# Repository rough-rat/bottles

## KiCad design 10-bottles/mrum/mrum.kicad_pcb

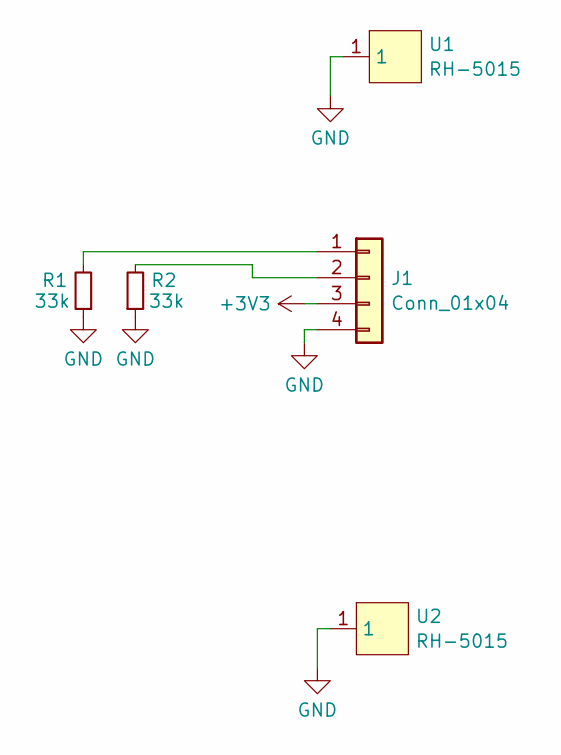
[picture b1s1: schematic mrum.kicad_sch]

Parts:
J1: Conn_01x04; PinHeader_1x04_P2.54mm_Vertical_SMD_Pin1Left
R1, R2: 33k; R_0603_1608Metric_Pad0.98x0.95mm_HandSolder
U1, U2: RH-5015; SMD_RH-5015; LCSC Part C5199798

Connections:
+3V3: J1.3
GND: J1.4, R1.1, R2.1, U1.1, U2.1
unnamed: J1.1, R1.2
unnamed: J1.2, R2.2

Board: 2 copper layers, 5 parts (5 on the bottom side), 3 nets, no tracks yet.

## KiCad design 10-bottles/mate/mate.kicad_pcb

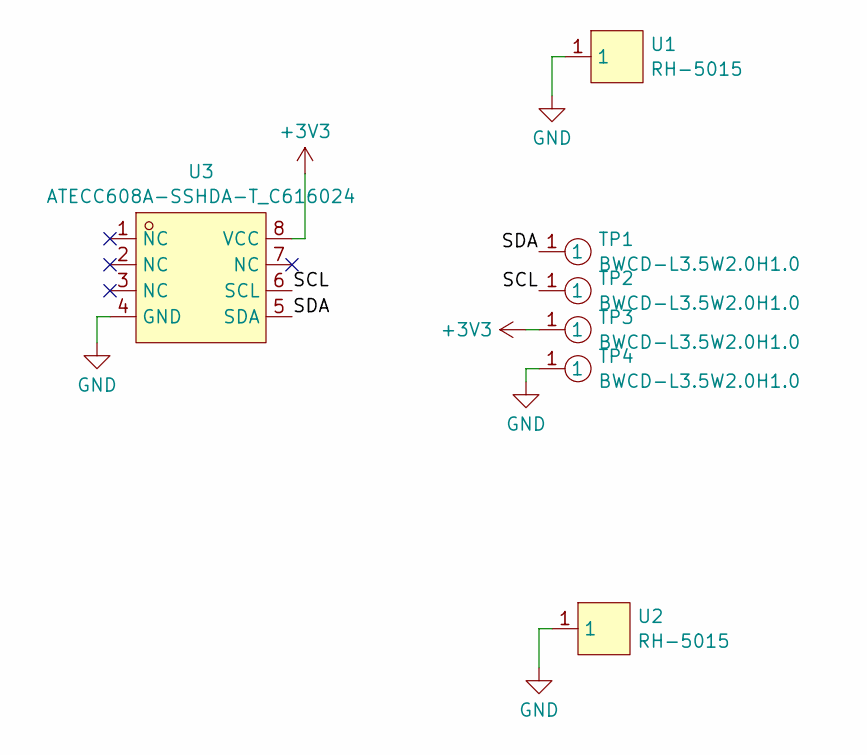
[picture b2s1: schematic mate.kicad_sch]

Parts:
TP1, TP2, TP3, TP4: BWCD-L3.5W2.0H1.0; SMD_BD2.0-L2.0-W2.0_C9900001905; LCSC Part C2826547
U1, U2: RH-5015; SMD_RH-5015; LCSC Part C5199798
U3: ATECC608A-SSHDA-T_C616024; SOIC-8_L4.9-W3.9-P1.27-LS6.0-BL; LCSC Part C616024

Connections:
+3V3: TP3.1, U3.8 (VCC)
/SCL: TP2.1, U3.6 (SCL)
/SDA: TP1.1, U3.5 (SDA)
GND: TP4.1, U1.1, U2.1, U3.4 (GND)

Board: 2 copper layers, 7 parts (7 on the bottom side), 4 nets, no tracks yet.

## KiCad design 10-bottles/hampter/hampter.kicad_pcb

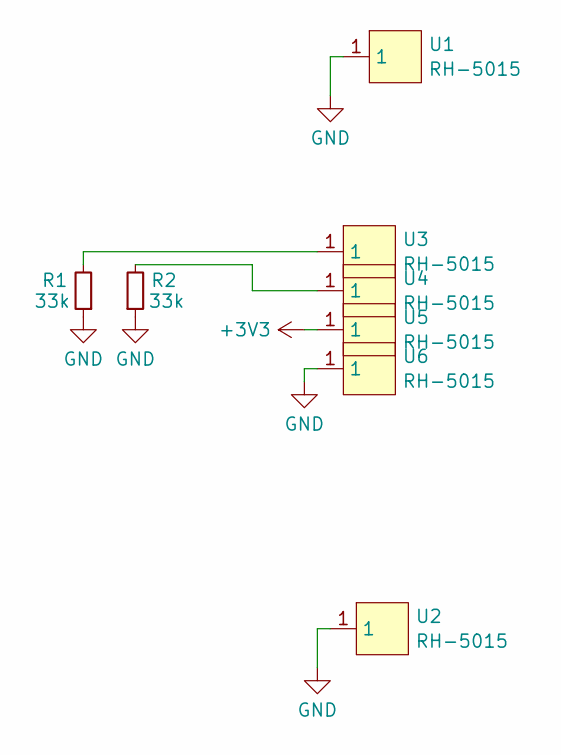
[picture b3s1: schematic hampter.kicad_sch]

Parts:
R1, R2: 33k; R_0603_1608Metric_Pad0.98x0.95mm_HandSolder
U1, U2, U3, U4, U5, U6: RH-5015; SMD_RH-5015; LCSC Part C5199798

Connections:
+3V3: U5.1
GND: R1.1, R2.1, U1.1, U2.1, U6.1
unnamed: R1.2, U3.1
unnamed: R2.2, U4.1

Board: 2 copper layers, 8 parts (8 on the bottom side), 3 nets, no tracks yet.

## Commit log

2024-11-21 add files and firmware stub
2024-11-30 add new bottles PoCs
2024-11-30 the rest of the botwl
